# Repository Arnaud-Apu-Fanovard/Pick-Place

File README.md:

# Pick-Place
 Pick and Place automatisée pour PCB designer

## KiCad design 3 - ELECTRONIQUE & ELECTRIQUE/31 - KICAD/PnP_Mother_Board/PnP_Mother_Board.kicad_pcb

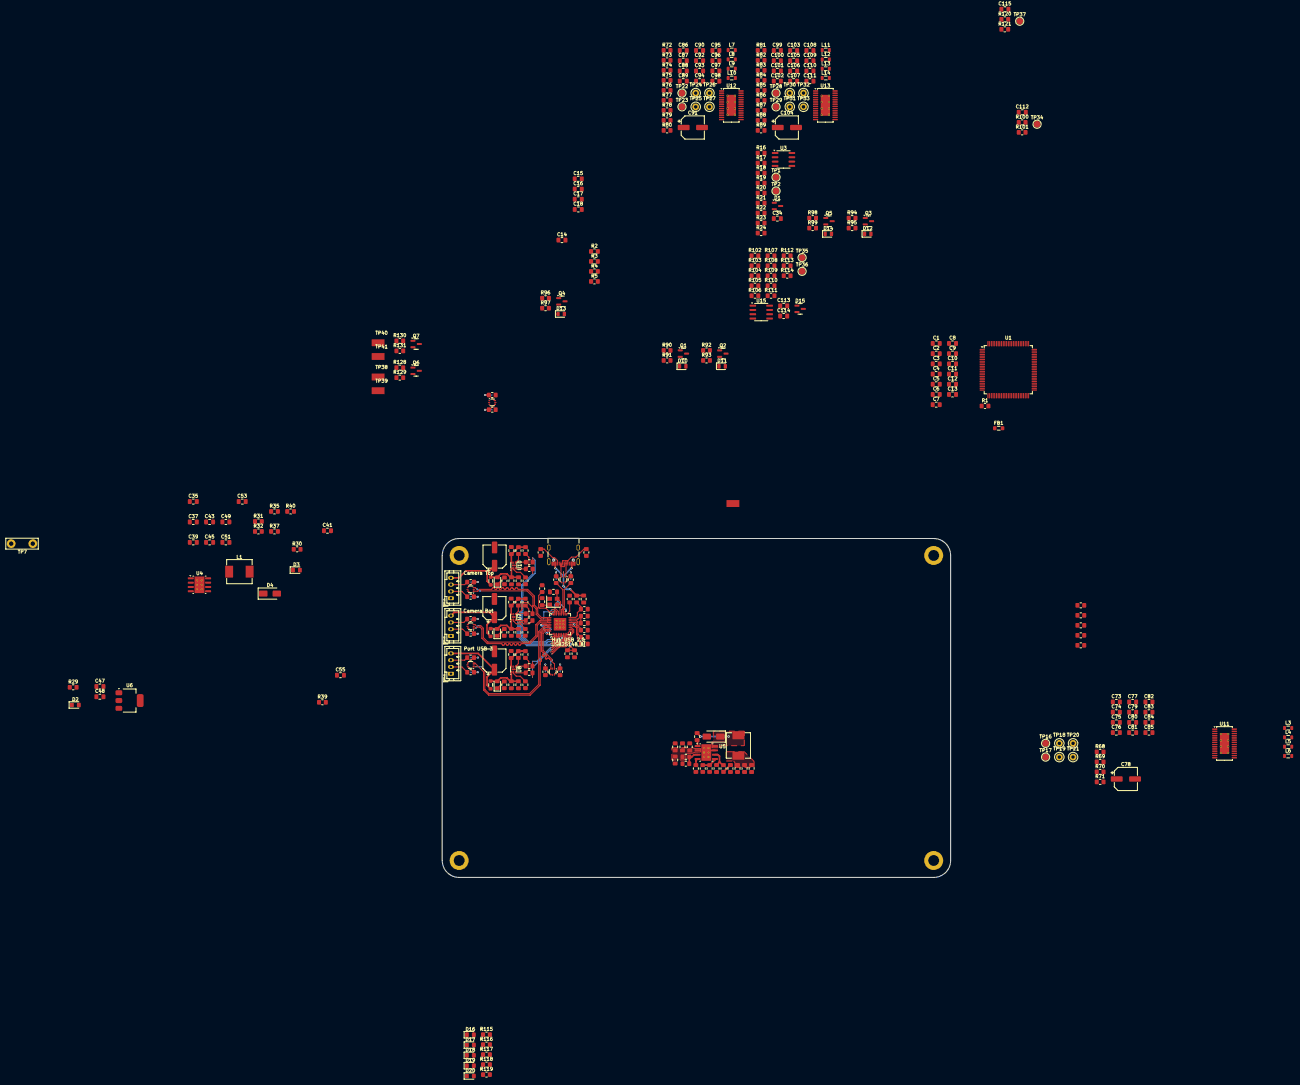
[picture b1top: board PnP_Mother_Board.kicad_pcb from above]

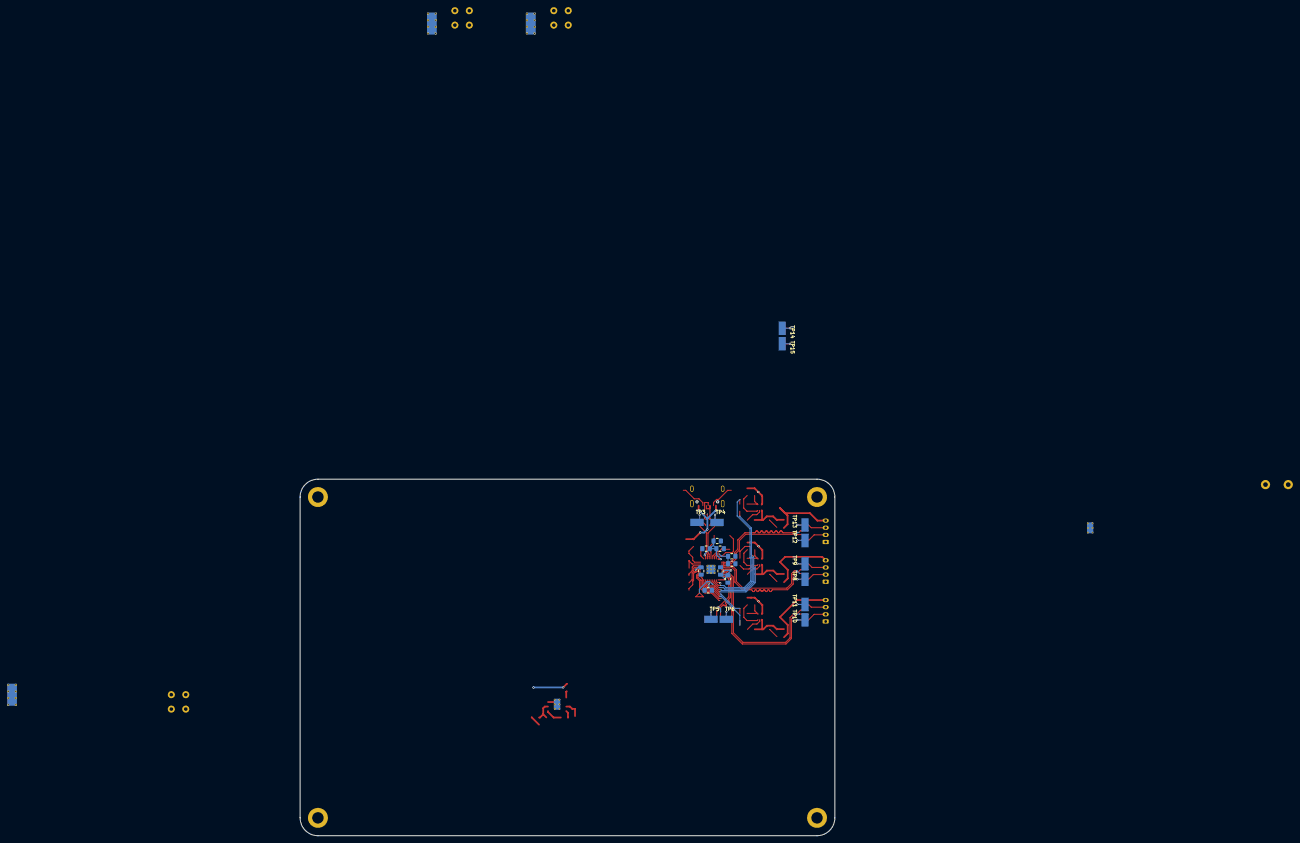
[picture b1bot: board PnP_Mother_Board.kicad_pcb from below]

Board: 4 copper layers, 150.0 x 100.0 mm, 356 parts (21 on the bottom side), 228 nets.

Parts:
C1, C76, C89, C102: 4.7uF; C_0805_2012Metric_Pad1.18x1.45mm_HandSolder
C2, C4, C57, C58, C59, C61, C62, C63, C69, C70, C71: 2.2uF; C_0805_2012Metric_Pad1.18x1.45mm_HandSolder
C3, C5, C6, C7, C8, C9, C10, C11, C12, C16, C17, C18, C22, C24, C28, C29, C30, C31, C32, C33, C49, C50, C74, C75, C77, C83, C84, C85, C87, C88, C90, C96, C97, C98, C100, C101, C103, C109, C110, C111, C112, C115: 0.1uF; C_0805_2012Metric_Pad1.18x1.45mm_HandSolder
C13, C21, C26, C27: 1uF; C_0805_2012Metric_Pad1.18x1.45mm_HandSolder
C14, C15, C23, C25: 10pF; C_0805_2012Metric_Pad1.18x1.45mm_HandSolder
C19, C20, C34, C114: 10nF; C_0805_2012Metric_Pad1.18x1.45mm_HandSolder
C35, C36, C37, C38, C39, C40, C41, C42: 2,2uF; C_0805_2012Metric_Pad1.18x1.45mm_HandSolder
C43, C44: 47pF; C_0805_2012Metric_Pad1.18x1.45mm_HandSolder
C45, C46: 4,7nF; C_0805_2012Metric_Pad1.18x1.45mm_HandSolder
C47, C48, C113: 10uF; C_0805_2012Metric_Pad1.18x1.45mm_HandSolder
C51, C52, C53, C54, C55, C56: 47uF; C_0805_2012Metric_Pad1.18x1.45mm_HandSolder
C60, C64, C72, C78, C91, C104: 100uF; CP_Elec_6.3x7.7
C73, C86, C99: 22nF; C_0805_2012Metric_Pad1.18x1.45mm_HandSolder
C79, C80, C81, C82, C92, C93, C94, C95, C105, C106, C107, C108: 470pF 24V; C_0805_2012Metric_Pad1.18x1.45mm_HandSolder
D1, D15: NUP2105L; SOT-23
D2, D3, D6, D7, D9, D16, D17, D18, D19, D20: LED; LED_0805_2012Metric_Pad1.15x1.40mm_HandSolder
D4, D5: B560C; D_SMA
D10, D11, D12, D13, D14: D; D_0805_2012Metric
FB1, FB2, FB3, FB5: 120R; L_0805_2012Metric_Pad1.05x1.20mm_HandSolder
H1, H2, H3, H4: MountingHole_Pad; MountingHole_3.2mm_M3_DIN965_Pad
IC1, IC2, IC3, IC4, IC5, IC6: USBLC6-2P6; SOT-666
J5: 629722000214; USB-C Wurth 16p
J6, J7, J8: Conn_01x04_Pin; JST_PH_B4B-PH-K_1x04_P2.00mm_Vertical
L1, L2: 7,2uH; L_Sunlord_MWSA0603S
L3, L4, L5, L6, L7, L8, L9, L10, L11, L12, L13, L14: L_Ferrite; L_0805_2012Metric
Q1, Q2, Q3, Q4, Q5, Q6, Q7: AO3400A; SOT-23
R1, R3, R4, R5, R7, R19, R20, R30, R42, R69, R78, R87, R90, R92, R94, R96, R98, R104, R105, R109, R110, R115, R116, R117, R118, R119, R128, R130: 10K; R_0805_2012Metric_Pad1.20x1.40mm_HandSolder
R2: 300r; R_0805_2012Metric_Pad1.20x1.40mm_HandSolder
R6, R15, R29: 5.1K; R_0805_2012Metric_Pad1.20x1.40mm_HandSolder
R8, R9, R10, R11, R12, R14: 100K; R_0805_2012Metric_Pad1.20x1.40mm_HandSolder
R13: 12K; R_0805_2012Metric_Pad1.20x1.40mm_HandSolder
R16, R17, R18, R23, R24, R25, R26, R27, R28, R43, R44, R48, R49, R53, R54, R55, R56, R57, R61, R62, R63, R64, R65, R66, R67, R72, R73, R74, R75, R76, R81, R82, R83, R84, R85, R102, R103, R106, R107, R108, R113, R114, R122, R123, R124: IR_0R; R_0805_2012Metric_Pad1.20x1.40mm_HandSolder
R21, R22, R111, R112: 60R; R_0805_2012Metric_Pad1.20x1.40mm_HandSolder
R31, R33: 442K; R_0805_2012Metric_Pad1.20x1.40mm_HandSolder
R32, R34: 90,9r; R_0805_2012Metric_Pad1.20x1.40mm_HandSolder
R35, R36: 16.9K; R_0805_2012Metric_Pad1.20x1.40mm_HandSolder
R37, R38: 243K; R_0805_2012Metric_Pad1.20x1.40mm_HandSolder
R39: 53,6K; R_0805_2012Metric_Pad1.20x1.40mm_HandSolder
R40: 10,2K; R_0805_2012Metric_Pad1.20x1.40mm_HandSolder
R41: 140K; R_0805_2012Metric_Pad1.20x1.40mm_HandSolder
R45, R50, R58, R125, R126, R127: DNP_12k; R_0805_2012Metric_Pad1.20x1.40mm_HandSolder
R46, R47, R51, R52, R59, R60: 330R; R_0805_2012Metric_Pad1.20x1.40mm_HandSolder
R68, R77, R86, R91, R93, R95, R97, R99, R129, R131: 1K; R_0805_2012Metric_Pad1.20x1.40mm_HandSolder
R70, R71, R79, R80, R88, R89: 120m; R_0805_2012Metric_Pad1.20x1.40mm_HandSolder
R100, R120: 5r; R_0805_2012Metric_Pad1.20x1.40mm_HandSolder
R101, R121: 5K; R_0805_2012Metric_Pad1.20x1.40mm_HandSolder
TP1, TP2, TP16, TP17, TP22, TP23, TP28, TP29, TP34, TP35, TP36, TP37: TestPoint; TestPoint_Pad_D2.0mm
TP3, TP5, TP8, TP10, TP12, TP14: D-; TestPoint_KEYSTONE_5029
TP4, TP6, TP9, TP11, TP13, TP15, TP42: D+; TestPoint_KEYSTONE_5029
TP7: TestPoint; TestPoint_Bridge_Pitch6.35mm_Drill1.3mm
TP18, TP19, TP20, TP21, TP24, TP25, TP26, TP27, TP30, TP31, TP32, TP33: TestPoint; TestPoint_Keystone_5000-5004_Miniature
TP38, TP39, TP40, TP41: TestPoint; TestPoint_KEYSTONE_5029
U1: STM32F407VETx; LQFP-100_14x14mm_P0.5mm
U2: USB2514B_Bi; QFN-36-1EP_6x6mm_P0.5mm_EP3.7x3.7mm_ThermalVias
U3: SN65HVD230; SOIC-8_3.9x4.9mm_P1.27mm
U4, U5: TPS54560BDDA; Texas_R-PDSO-G8_EP2.95x4.9mm_Mask2.4x3.1mm_ThermalVias
U6: LM1117MPX-33NOPB; SOT-223
U7, U8, U10: MIC2099-1YMT-TR; MLF-6-1EP_1.6x1.6mm_P0.5mm_EP0.5x1.26mm
U11, U12, U13: TMC2226-SA; HTSSOP-28-1EP_4.4x9.7mm_P0.65mm_EP2.75x6.2mm_ThermalVias
U15: MAX485E; SOIC-8_3.9x4.9mm_P1.27mm
Y2: CFPX-180; Crystal_SMD_3225-4Pin_3.2x2.5mm

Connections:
+3.3V: C1.1, C3.1, C5.1, C6.1, C8.1, C9.1, C10.1, C11.1, C12.1, C27.1, C28.1, C29.1, C30.1, C31.1, C32.1, C33.1, C48.1, C75.1, C88.1, C101.1, C113.1, FB1.1, R3.2, R4.2, R5.2, R7.1, R18.1, R19.2, R20.2, R29.1, R69.2, R78.2, R87.2, R100.1, R104.1, R105.1, R109.2, R110.2, R120.1, U1.6 (VBAT), U1.11 (VDD), U1.19 (VDD), U1.22 (VDDA), U1.28 (VDD), U1.50 (VDD), U1.75 (VDD), U1.100 (VDD), U2.5 (VDDA33), U2.10 (VDDA33), U2.15 (VDD33), U2.23 (VDD33), U2.29 (VDDA33), U2.36 (VDDA33), U3.3 (VCC), U6.2 (OUT), U6.4 (OUT), U11.19 (VCC_IO), U12.19 (VCC_IO), U13.19 (VCC_IO), U15.8 (VCC)
+5V: C47.1, C51.1, C53.1, C55.1, C57.1, C61.1, C69.1, L1.2, R30.1, R39.1, R45.1, R50.1, R58.1, R125.1, R126.1, R127.1, U6.3 (IN), U7.6 (VIN), U8.6 (VIN), U10.6 (VIN)
+12V: C52.1, C54.1, C56.1, C74.1, C78.1, C83.1, C85.1, C87.1, C91.1, C96.1, C98.1, C100.1, C104.1, C109.1, C111.1, D10.1 (K), D11.1 (K), D12.1 (K), D13.1 (K), D14.1 (K), L2.2, R41.1, U11.3 (VS), U11.26 (VS), U12.3 (VS), U12.26 (VS), U13.3 (VS), U13.26 (VS)
+24V: C35.1, C36.1, C37.1, C38.1, C39.1, C40.1, C41.1, C42.1, R31.1, R33.1, U4.2 (VIN), U5.2 (VIN)
+VDD_USB: C26.1, IC1.5 (VBUS), J5.A4 (VBUS), J5.A9 (VBUS1), J5.B4 (VBUS3), J5.B9 (VBUS2), R9.1
/MCU/ACD1_IN0: R101.2, TP34.1, U1.23 (PA0)
/MCU/ACD1_IN1: R121.2, TP37.1, U1.24 (PA1)
/MCU/CAN1_RX: R16.1, U1.81 (PD0)
/MCU/CAN1_TX: R17.1, U1.82 (PD1)
/MCU/CAN_Bus/CAN+: D1.2 (K), R21.1, R23.1, U3.7 (CANH)
/MCU/CAN_Bus/CAN-: D1.1 (K), R22.2, R24.1, U3.6 (CANL)
/MCU/DIAG_R1: R67.1, U1.41 (PE10)
/MCU/DIAG_R2: R76.1, U1.46 (PE15)
/MCU/DIAG_Z: R85.1, U1.36 (PB1)
/MCU/DIR_R1: R65.2, U1.39 (PE8)
/MCU/DIR_R2: R74.2, U1.44 (PE13)
/MCU/DIR_Z: R83.2, U1.34 (PC5)
/MCU/Drive_Stepper_R1/A1: C79.1, L3.2, TP18.1
/MCU/Drive_Stepper_R1/A2: C80.2, L4.2, TP19.1
/MCU/Drive_Stepper_R1/B1: C81.1, L5.2, TP20.1
/MCU/Drive_Stepper_R1/B2: C82.2, L6.2, TP21.1
/MCU/Drive_Stepper_R2/A1: C92.1, L7.2, TP24.1
/MCU/Drive_Stepper_R2/A2: C93.2, L8.2, TP25.1
/MCU/Drive_Stepper_R2/B1: C94.1, L9.2, TP26.1
/MCU/Drive_Stepper_R2/B2: C95.2, L10.2, TP27.1
/MCU/Drive_Stepper_Z/A1: C105.1, L11.2, TP30.1
/MCU/Drive_Stepper_Z/A2: C106.2, L12.2, TP31.1
/MCU/Drive_Stepper_Z/B1: C107.1, L13.2, TP32.1
/MCU/Drive_Stepper_Z/B2: C108.2, L14.2, TP33.1
/MCU/EN_R1: R66.1, U1.38 (PE7)
/MCU/EN_R2: R75.1, U1.43 (PE12)
/MCU/EN_Z: R84.1, U1.33 (PC4)
/MCU/LED_1: R115.1, U1.1 (PE2)
/MCU/LED_2: R116.1, U1.2 (PE3)
/MCU/LED_3: R117.1, U1.3 (PE4)
/MCU/LED_4: R118.1, U1.4 (PE5)
/MCU/LED_5: R119.1, U1.5 (PE6)
/MCU/LS_X: C16.1, R3.1, U1.7 (PC13)
/MCU/LS_Y: C17.1, R4.1, U1.8 (PC14)
/MCU/LS_Z: C18.1, R5.1, U1.9 (PC15)
/MCU/Mosfet_Distributeur1: R96.2, R97.1, U1.87 (PD6)
/MCU/Mosfet_Distributeur2: R98.2, R99.1, U1.88 (PD7)
/MCU/Mosfet_Fan: R92.2, R93.1, U1.84 (PD3)
/MCU/Mosfet_Light_Bottom: R128.2, R129.1
/MCU/Mosfet_Light_Top: R130.2, R131.1
/MCU/Mosfet_Pompe1: R90.2, R91.1, U1.85 (PD4)
/MCU/Mosfet_Pompe2: R94.2, R95.1, U1.86 (PD5)
/MCU/RS485/A/B+: D15.2 (K), R111.1, R113.1, U15.6 (A)
/MCU/RS485/A/B-: D15.1 (K), R112.2, R114.1, U15.7 (B)
/MCU/RS485_EN: R102.1, R103.1, U1.80 (PC12)
/MCU/STEP_R1: R64.1, U1.40 (PE9)
/MCU/STEP_R2: R73.1, U1.45 (PE14)
/MCU/STEP_Z: R82.1, U1.35 (PB0)
/MCU/UART4_RX: R106.1, U1.79 (PC11)
/MCU/UART4_TX: R108.1, U1.78 (PC10)
/MCU/UART_R1: R63.1, U1.37 (PB2)
/MCU/UART_R2: R72.1, U1.42 (PE11)
/MCU/UART_Z: R81.1, U1.32 (PA7)
/MCU/XTAL_IN: C14.2, U1.12 (PH0)
/MCU/XTAL_OUT: R2.2, U1.13 (PH1)
/USB/D_N: IC1.1 (I/O1_1), J5.A7 (D-1), J5.B7 (D-2)
/USB/D_P: IC1.3 (I/O2_1), J5.A6 (D+1), J5.B6 (D+2)
/USB/ESD_Prot_DownStream1/D+: J8.3, R57.2
/USB/ESD_Prot_DownStream1/D-: J8.2, R56.1
/USB/ESD_Prot_DownStream1/VDD: C72.1, FB5.2, IC5.5 (VBUS), J8.4
/USB/ESD_Prot_DownStream2/D+: J6.3, R44.2
/USB/ESD_Prot_DownStream2/D-: J6.2, R43.1
/USB/ESD_Prot_DownStream2/VDD: C60.1, FB2.2, IC3.5 (VBUS), J6.4
/USB/ESD_Prot_DownStream3/D+: J7.3, R49.2
/USB/ESD_Prot_DownStream3/D-: J7.2, R48.1
/USB/ESD_Prot_DownStream3/VDD: C64.1, FB3.2, IC4.5 (VBUS), J7.4
/USB/Host D+: R26.2, U2.31 (USBDP_UP)
/USB/Host D-: R25.1, U2.30 (USBDM_UP)
/USB/Power_Distribution_Switch1/NOCS: R58.2, R124.2, U10.3 (FAULT/)
/USB/Power_Distribution_Switch1/PWRTPWR: R55.2, R127.2, U10.4 (ENABLE/)
/USB/Power_Distribution_Switch2/NOCS: R45.2, R122.2, U7.3 (FAULT/)
/USB/Power_Distribution_Switch2/PWRTPWR: R53.2, R125.2, U7.4 (ENABLE/)
/USB/Power_Distribution_Switch3/NOCS: R50.2, R123.2, U8.3 (FAULT/)
/USB/Power_Distribution_Switch3/PWRTPWR: R54.2, R126.2, U8.4 (ENABLE/)
/USB/USB HUB1+: IC5.3 (I/O2_1), U2.2 (USBDP_DN1/PRT_DIS_P1)
/USB/USB HUB1-: IC5.1 (I/O1_1), U2.1 (USBDM_DN1/PRT_DIS_M1)
/USB/USB HUB2+: IC3.3 (I/O2_1), U2.4 (USBDP_DN2/PRT_DIS_P2)
/USB/USB HUB2-: IC3.1 (I/O1_1), U2.3 (USBDM_DN2/PRT_DIS_M2)
/USB/USB HUB3+: IC4.3 (I/O2_1), U2.7 (USBDP_DN3/PRT_DIS_P3)
/USB/USB HUB3-: IC4.1 (I/O1_1), U2.6 (USBDM_DN3/PRT_DIS_M3)
/USB/USB HUB4+: IC2.3 (I/O2_1), U2.9 (USBDP_DN4/PRT_DIS_P4)
/USB/USB HUB4-: IC2.1 (I/O1_1), U2.8 (USBDM_DN4/PRT_DIS_M4)
/USB/USB HUB NOCS1: R124.1, U2.13 (OCS_N1)
/USB/USB HUB NOCS2: R122.1, U2.17 (OCS_N2)
/USB/USB HUB NOCS3: R123.1, U2.19 (OCS_N3)
/USB/USB PWRTPWR1: R55.1, U2.12 (PRTPWR1/BC_EN1)
/USB/USB PWRTPWR2: R53.1, U2.16 (PRTPWR2/BC_EN2)
/USB/USB PWRTPWR3: R54.1, U2.18 (PRTPWR3/BC_EN3)
/USB/XTAL_IN: C23.2, U2.33 (XTALIN/CLKIN), Y2.1
/USB/XTAL_OUT: C25.1, U2.32 (XTALOUT), Y2.3
GND: C1.2, C2.2, C3.2, C4.2, C5.2, C6.2, C7.2, C8.2, C9.2, C10.2, C11.2, C12.2, C13.2, C14.1, C15.2, C16.2, C17.2, C18.2, C19.2, C20.2, C21.2, C22.2, C23.1, C24.2, C25.2, C26.2, C27.2, C28.2, C29.2, C30.2, C31.2, C32.2, C33.2, C34.2, C35.2, C36.2, C37.2, C38.2, C39.2, C40.2, C41.2, C42.2, C43.2, C44.2, C45.2, C46.2, C47.2, C48.2, C51.2, C52.2, C53.2, C54.2, C55.2, C56.2, C57.2, C58.2, C59.2, C60.2, C61.2, C62.2, C63.2, C64.2, C69.2, C70.2, C71.2, C72.2, C75.2, C76.2, C77.2, C78.2, C79.2, C80.1, C81.2, C82.1, C83.2, C84.2, C85.2, C88.2, C89.2, C90.2, C91.2, C92.2, C93.1, C94.2, C95.1, C96.2, C97.2, C98.2, C101.2, C102.2, C103.2, C104.2, C105.2, C106.1, C107.2, C108.1, C109.2, C110.2, C111.2, C112.2, C113.2, C114.2, C115.2, D1.3 (A), D2.1 (K), D3.1 (K), D4.2 (A), D5.2 (A), D15.3 (A), D16.1 (K), D17.1 (K), D18.1 (K), D19.1 (K), D20.1 (K), H1.1, H2.1, H3.1, H4.1, IC1.2 (GND), IC2.2 (GND), IC3.2 (GND), IC4.2 (GND), IC5.2 (GND), IC6.2 (GND), J5.A1 (GND), J5.A12 (GND1), J5.B1 (GND3), J5.B12 (GND2), J5.S1, J5.S2, J5.S3, J5.S4, J6.1, J7.1, J8.1, Q1.2 (S), Q2.2 (S), Q3.2 (S), Q4.2 (S), Q5.2 (S), Q6.2 (S), Q7.2 (S), R6.2, R8.2, R10.2, R11.2, R12.2, R13.2, R14.2, R15.2, R32.2, R34.2, R37.2, R38.2, R40.2, R42.2, R46.2, R47.2, R51.2, R52.2, R59.2, R60.2, R70.1, R71.1, R79.1, R80.1, R88.1, R89.1, R90.1, R92.1, R94.1, R96.1, R98.1, R101.1, R121.1, R128.1, R130.1, TP7.1, U1.10 (VSS), U1.20 (VSSA), U1.27 (VSS), U1.74 (VSS), U1.99 (VSS), U2.11 (TEST), U2.37 (VSS), U3.2 (GND), U3.8 (Rs), U4.7 (GND), U4.9 (GND), U5.7 (GND), U5.9 (GND), U6.1 (GND), U7.5 (GND), U8.5 (GND), U10.5 (GND), U11.6 (GND), U11.12 (MS1_AD0), U11.13 (NC), U11.14 (MS2_AD1), U11.17 (CLK), U11.22 (GND), U11.29 (GND), U12.6 (GND), U12.12 (MS1_AD0), U12.13 (NC), U12.14 (MS2_AD1), U12.17 (CLK), U12.22 (GND), U12.29 (GND), U13.6 (GND), U13.12 (MS1_AD0), U13.13 (NC), U13.14 (MS2_AD1), U13.17 (CLK), U13.22 (GND), U13.29 (GND), U15.5 (GND), Y2.2, Y2.4
unnamed: C13.1, FB1.2
unnamed: C15.1, R2.1
unnamed: C34.1, R21.2, R22.1
unnamed: C45.1, R35.2
unnamed: C46.1, R36.2
unnamed: C112.1, R100.2
unnamed: C114.1, R111.2, R112.1
unnamed: C115.1, R120.2
unnamed: D2.2 (A), R29.2
unnamed: D3.2 (A), R30.2
unnamed: C49.2, D4.1 (K), L1.1, U4.8 (SW)
unnamed: C50.2, D5.1 (K), L2.1, U5.8 (SW)
unnamed: C58.1, C59.1, D6.2 (A), FB2.1, U7.1 (VOUT)
unnamed: D6.1 (K), R47.1
unnamed: C62.1, C63.1, D7.2 (A), FB3.1, U8.1 (VOUT)
unnamed: D7.1 (K), R52.1
unnamed: C70.1, C71.1, D9.2 (A), FB5.1, U10.1 (VOUT)
unnamed: D9.1 (K), R60.1
unnamed: D10.2 (A), Q1.3 (D)
unnamed: D11.2 (A), Q2.3 (D)
unnamed: D12.2 (A), Q3.3 (D)
unnamed: D13.2 (A), Q4.3 (D)
unnamed: D14.2 (A), Q5.3 (D)
unnamed: D16.2 (A), R115.2
unnamed: D17.2 (A), R116.2
unnamed: D18.2 (A), R117.2
unnamed: D19.2 (A), R118.2
unnamed: D20.2 (A), R119.2
unnamed: IC1.6 (I/O1_2), R25.2
unnamed: IC1.4 (I/O2_2), R26.1
unnamed: IC2.6 (I/O1_2), R27.2
unnamed: IC2.4 (I/O2_2), R28.1
unnamed: IC3.6 (I/O1_2), R43.2
unnamed: IC3.4 (I/O2_2), R44.1
unnamed: IC4.6 (I/O1_2), R48.2
unnamed: IC4.4 (I/O2_2), R49.1
unnamed: IC5.6 (I/O1_2), R56.2
unnamed: IC5.4 (I/O2_2), R57.1
unnamed: IC6.6 (I/O1_2), R61.2
unnamed: IC6.4 (I/O2_2), R62.1
unnamed: J5.A5 (CC1), R6.1
unnamed: J5.B5 (CC2), R15.1
unnamed: Q1.1 (G), R91.2
unnamed: Q2.1 (G), R93.2
unnamed: Q3.1 (G), R95.2
unnamed: Q4.1 (G), R97.2
unnamed: Q5.1 (G), R99.2
unnamed: Q6.1 (G), R129.2
unnamed: Q7.1 (G), R131.2
unnamed: R63.2, R68.2
unnamed: R72.2, R77.2
unnamed: R81.2, R86.2
unnamed: R1.2, U1.94 (BOOT0)
unnamed: C7.1, U1.14 (NRST)
unnamed: C2.1, U1.49 (VCAP_1)
unnamed: C4.1, U1.73 (VCAP_2)
unnamed: C20.1, C24.1, U2.14 (CRFILT)
unnamed: R14.1, U2.25 (HS_IND/CFG_SEL1)
unnamed: C19.1, C22.1, U2.34 (PLLFILT)
unnamed: R13.1, U2.35 (RBIAS)
unnamed: C21.1, R7.2, U2.26 (RESET_N)
unnamed: R8.1, U2.24 (SCL/SMBCLK/CFG_SEL0)
unnamed: R10.1, U2.22 (SDA/SMBDATA/NON_REM1)
unnamed: R12.1, U2.28 (SUSP_IND/LOCAL_PWR/NON_REM0)
unnamed: R9.2, R11.1, U2.27 (VBUS_DET)
unnamed: R16.2, R19.1, TP1.1, U3.1 (D)
unnamed: R17.2, R20.1, TP2.1, U3.4 (R)
unnamed: R18.2, U3.5 (Vref)
unnamed: C49.1, U4.1 (BOOT)
unnamed: C43.1, R35.1, U4.6 (COMP)
unnamed: R31.2, R32.1, U4.3 (EN)
unnamed: R39.2, R40.1, U4.5 (FB)
unnamed: R37.1, U4.4 (RT/CLK)
unnamed: C50.1, U5.1 (BOOT)
unnamed: C44.1, R36.1, U5.6 (COMP)
unnamed: R33.2, R34.1, U5.3 (EN)
unnamed: R41.2, R42.1, U5.5 (FB)
unnamed: R38.1, U5.4 (RT/CLK)
unnamed: R46.1, U7.2 (ILIMIT)
unnamed: R51.1, U8.2 (ILIMIT)
unnamed: R59.1, U10.2 (ILIMIT)
unnamed: C76.1, U11.11 (5VOUT)
unnamed: C84.1, R71.2, U11.27 (BRA)
unnamed: C77.1, R70.2, U11.2 (BRB)
unnamed: C73.2, U11.8 (CPI)
unnamed: C73.1, U11.7 (CPO)
unnamed: R67.2, U11.15 (DIAG)
unnamed: R65.1, U11.23 (DIR)
unnamed: L3.1, U11.28 (OA1)
unnamed: L4.1, U11.25 (OA2)
unnamed: L5.1, U11.1 (OB1)
unnamed: L6.1, U11.4 (OB2)
unnamed: R68.1, TP16.1, U11.18 (PDN_UART)
unnamed: R64.2, U11.20 (STEP)
unnamed: C74.2, U11.9 (VCP)
unnamed: R66.2, R69.1, TP17.1, U11.5 (~EN)
unnamed: C89.1, U12.11 (5VOUT)
unnamed: C97.1, R80.2, U12.27 (BRA)
unnamed: C90.1, R79.2, U12.2 (BRB)
unnamed: C86.2, U12.8 (CPI)
unnamed: C86.1, U12.7 (CPO)
unnamed: R76.2, U12.15 (DIAG)
unnamed: R74.1, U12.23 (DIR)
unnamed: L7.1, U12.28 (OA1)
unnamed: L8.1, U12.25 (OA2)
unnamed: L9.1, U12.1 (OB1)
unnamed: L10.1, U12.4 (OB2)
unnamed: R77.1, TP22.1, U12.18 (PDN_UART)
unnamed: R73.2, U12.20 (STEP)
unnamed: C87.2, U12.9 (VCP)
unnamed: R75.2, R78.1, TP23.1, U12.5 (~EN)
unnamed: C102.1, U13.11 (5VOUT)
unnamed: C110.1, R89.2, U13.27 (BRA)
unnamed: C103.1, R88.2, U13.2 (BRB)
unnamed: C99.2, U13.8 (CPI)
unnamed: C99.1, U13.7 (CPO)
unnamed: R85.2, U13.15 (DIAG)
unnamed: R83.1, U13.23 (DIR)
unnamed: L11.1, U13.28 (OA1)
unnamed: L12.1, U13.25 (OA2)
unnamed: L13.1, U13.1 (OB1)
unnamed: L14.1, U13.4 (OB2)
unnamed: R86.1, TP28.1, U13.18 (PDN_UART)
unnamed: R82.2, U13.20 (STEP)
unnamed: C100.2, U13.9 (VCP)
unnamed: R84.2, R87.1, TP29.1, U13.5 (~EN)
unnamed: R103.2, R105.2, R107.1, U15.3 (DE)
unnamed: R108.2, R110.1, TP36.1, U15.4 (DI)
unnamed: R106.2, R109.1, TP35.1, U15.1 (RO)
unnamed: R102.2, R104.2, R107.2, U15.2 (~RE)
STM32_D+: IC6.3 (I/O2_1), R28.2, U1.71 (PA12)
STM32_D-: IC6.1 (I/O1_1), R27.1, U1.70 (PA11)

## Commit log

2025-01-16 Create Testgithub.txt
    creation testgithub
2025-01-17 Commit_0.0 Creation of the folders
2025-01-20 Commit_0.01 Programme Aide Formules Mécanique
2025-01-31 Add docs
2025-01-31 Orgranisation Notion
2025-02-05 Cahier des charges et diagramme pieuvre
2025-02-05 Cdcf
2025-02-19 Cahier des charges, Diagramme Pieuvre
2025-04-08 Carte mère
